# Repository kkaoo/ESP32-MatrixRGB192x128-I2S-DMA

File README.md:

# RGBMatrixPanel library for the ESP32, utilising I2S DMA

得到[mrfaptastic](https://github.com/mrfaptastic/ESP32-RGB64x32MatrixPanel-I2S-DMA)启发, fork并扩展了功能：

* 修改了IO映射，留出SPI接口可以扩展连接树莓派
* 关掉了双buffer功能，留存更多的RAM来扩展更大的显示屏：192x128
* 受SPI接口速度限制，外部SPI显示传输刷新率只有20HZ
* RAM限制和DMA输出频率限制，RGB Panel刷新率只有70HZ，会有一点闪烁感
* can theoretically provide 5 bit colour: RGB555

## Usage

* 如果不需要那么高的亮度，可以将亮度调低减小电流:
`matrix.setPanelBrightness(8);`
* 注意有的面板LED接口顺序是RGB，有的则是BGR，还有RBG，有时需要调整IO，可以在直接matrix.begin()函数重新分配IO
`matrix.begin(R1,G1,B1,R2,G2,B2.....)`
* 暂时没测试FM612X系列驱动IC的面板，这类IC比较特殊，需要定义锁存脉冲个数
* 开发环境PlatformIO
* 如果连接6个面板，我是这样排列的

* 测试64x64的效果[examples/test_64x64/test_64x64.cpp]

`#define mw 64`

`#define mh 64`

* 测试192x128的效果[examples/test_192x128/test_192x128.cpp]

`#define mw 192`

`#define mh 128`

## Circuit & PCB

By default the pin mapping is as follows (defaults defined in ESP32-RGBMatrixPanel-I2S-DMA.h).

请注意线路是按单个面板画的（64x64），如果拼接多个面板，电源需要加强加强再加强。即单独外加5V/3A以上电源。

## 连接树莓派或其它

通过SPI接口连接到树莓派，RGBMatrixPanel模拟成一块SPI TFT显示屏。

......待续

## Credits

* ['ESP32-RGB64x32MatrixPanel-I2S-DMA' library](https://github.com/mrfaptastic/ESP32-RGB64x32MatrixPanel-I2S-DMA)
* ['SmartMatrix' project code](https://github.com/pixelmatix/SmartMatrix/tree/teensylc)
* [Sprite_TM's demo implementation here](https://www.esp32.com/viewtopic.php?f=17&t=3188)

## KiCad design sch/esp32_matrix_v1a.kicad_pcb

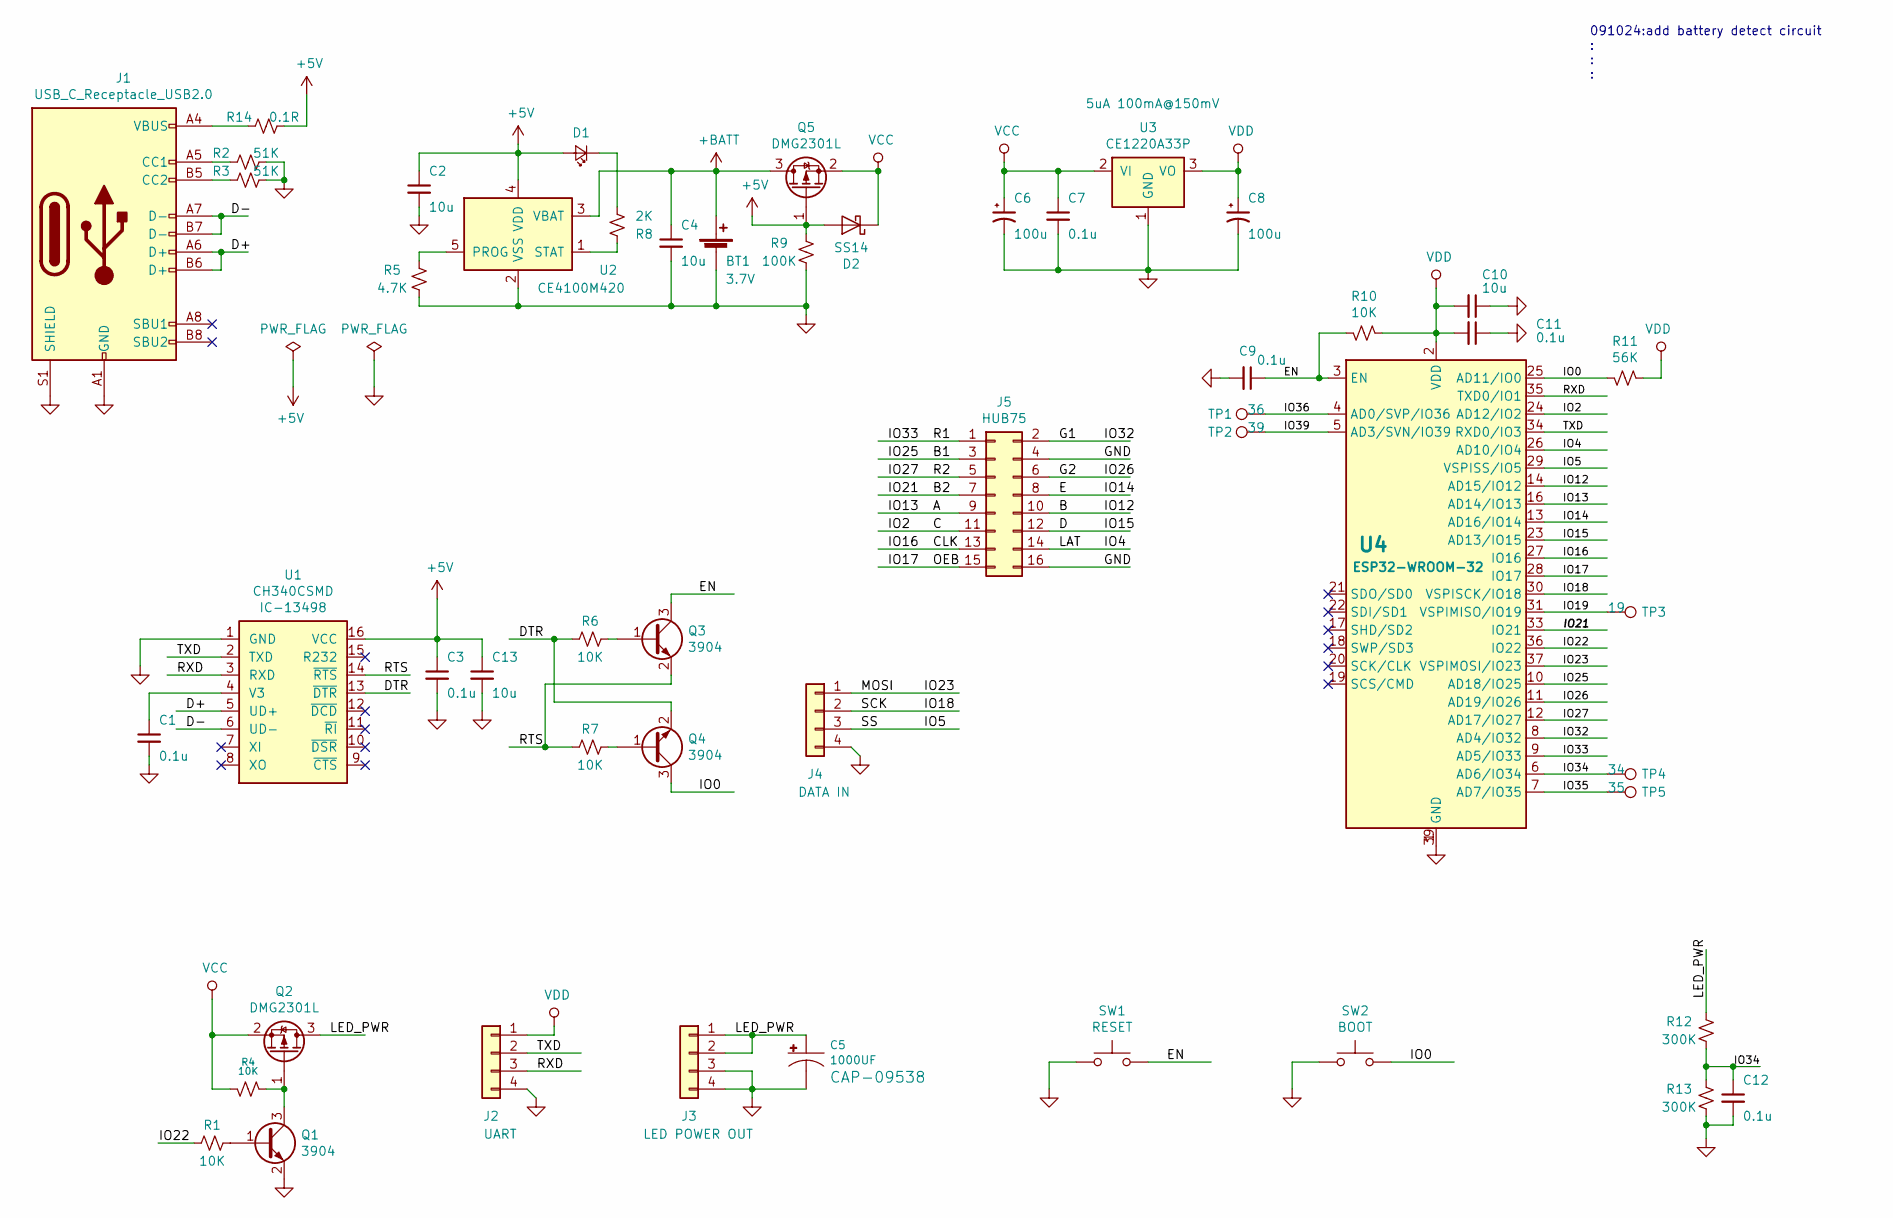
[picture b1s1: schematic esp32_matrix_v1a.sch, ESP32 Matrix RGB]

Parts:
BT1: 3.7V; JST_PH_B2B-PH-K_1x02_P2.00mm_Vertical
C1, C3, C7, C9, C11, C12: 0.1u; 0603_C
C2, C4, C10, C13: 10u; 0805_C
C5: 1000UF; CPOL-RADIAL-5MM-10MM
C6, C8: 100u; CP_EIA-3528-15_AVX-H
D1: LED_Small; LED_0805_2012Metric
D2: SS14; D_SMA
J1: USB_C_Receptacle_USB2.0; USB_C_Receptacle_Palconn_UTC16-G
J2: UART; 1X04_NO_SILK
J3: LED POWER OUT; 1X04_NO_SILK
J4: DATA IN; 1X04_NO_SILK
J5: HUB75; PinSocket_2x08_P2.54mm_Vertical
Q1, Q3, Q4: 3904; SOT-23
Q2, Q5: DMG2301L; SOT-23
R1, R4, R6, R7, R10: 10K; 0603_R
R2, R3: 51K; 0603_R
R5: 4.7K; 0603_R
R8: 2K; 0603_R
R9: 100K; 0603_R
R11: 56K; 0603_R
R12, R13: 300K; 0603_R
R14: 0.1R; 0603_R
SW1: RESET; SW_Push_1P1T_NO_CK_KSC6xxJ
SW2: BOOT; SW_Push_1P1T_NO_CK_KSC6xxJ
TP1: 36; TestPoint_Pad_D1.0mm
TP2: 39; TestPoint_Pad_D1.0mm
TP3: 19; TestPoint_Pad_D1.0mm
TP4: 34; TestPoint_Pad_D1.0mm
TP5: 35; TestPoint_Pad_D1.0mm
U1: CH340CSMD; SO16
U2: CE4100M420; SOT-23-5
U3: CE1220A33P; SOT-89-3
U4: ESP32-WROOM-32

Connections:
+BATT: BT1.1 (+), C4.1, Q5.3 (D), U2.3 (VBAT)
/A: J5.9, U4.16 (AD14/IO13)
/B: J5.10, U4.14 (AD15/IO12)
/BD1: J5.3, U4.10 (AD18/IO25)
/BD2: J5.7, U4.33 (IO21)
/C: J5.11, U4.24 (AD12/IO2)
/CLK: J5.13, U4.27 (IO16)
/D: J5.12, U4.23 (AD13/IO15)
/D+: J1.A6 (D+), J1.B6 (D+), U1.5 (UD+)
/D-: J1.A7 (D-), J1.B7 (D-), U1.6 (UD-)
/DTR: Q4.2 (E), R6.2, U1.13 (~DTR)
/E: J5.8, U4.13 (AD16/IO14)
/EN: C9.1, Q3.3 (C), R10.1, SW1.2, U4.3 (EN)
/GD1: J5.2, U4.8 (AD4/IO32)
/GD2: J5.6, U4.11 (AD19/IO26)
/IO0: Q4.3 (C), R11.1, SW2.2, U4.25 (AD11/IO0)
/IO4: J5.14, U4.26 (AD10/IO4)
/IO5: J4.3, U4.29 (VSPISS/IO5)
/IO17: J5.15, U4.28 (IO17)
/IO18: J4.2, U4.30 (VSPISCK/IO18)
/IO19: TP3.1, U4.31 (VSPIMISO/IO19)
/IO22: R1.2, U4.36 (IO22)
/IO23: J4.1, U4.37 (VSPIMOSI/IO23)
/IO27: J5.5, U4.12 (AD17/IO27)
/IO33: J5.1, U4.9 (AD5/IO33)
/IO34: C12.1, R12.1, R13.2, TP4.1, U4.6 (AD6/IO34)
/IO35: TP5.1, U4.7 (AD7/IO35)
/IO36: TP1.1, U4.4 (AD0/SVP/IO36)
/IO39: TP2.1, U4.5 (AD3/SVN/IO39)
/LED_PWR: C5.+, J3.1, J3.2, Q2.3 (D), R12.2
/RTS: Q3.2 (E), R7.2, U1.14 (~RTS)
/RXD: J2.3, U1.3 (RXD), U4.35 (TXD0/IO1)
/TXD: J2.2, U1.2 (TXD), U4.34 (RXD0/IO3)
GND: BT1.2 (-), C1.2, C2.2, C3.2, C4.2, C5.-, C6.2, C7.2, C8.2, C9.2, C10.1, C11.1, C12.2, C13.2, J1.A1 (GND), J1.A12 (GND), J1.B1 (GND), J1.B12 (GND), J1.S1 (SHIELD), J2.4, J3.3, J3.4, J4.4, J5.4, J5.16, Q1.2 (E), R2.1, R3.1, R5.1, R9.1, R13.1, SW1.1, SW2.1, U1.1 (GND), U2.2 (VSS), U3.1 (GND), U4.1 (GND), U4.15 (GND), U4.38 (GND), U4.39 (GND)
unnamed: C1.1, U1.4 (V3)
unnamed: D1.1 (K), R8.1
unnamed: J1.A5 (CC1), R2.2
unnamed: J1.B5 (CC2), R3.2
unnamed: Q1.1 (B), R1.1
unnamed: Q1.3 (C), Q2.1 (G), R4.2
unnamed: Q3.1 (B), R6.1
unnamed: Q4.1 (B), R7.1
unnamed: R5.2, U2.5 (PROG)
unnamed: R8.2, U2.1 (STAT)
VCC: C6.1, C7.1, D2.1 (K), Q2.2 (S), Q5.2 (S), R4.1, U3.2 (VI)
VDD: C8.1, C10.2, C11.2, J2.1, R10.2, R11.2, U3.3 (VO), U4.2 (VDD)

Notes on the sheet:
091024:add battery detect circuit : : :

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
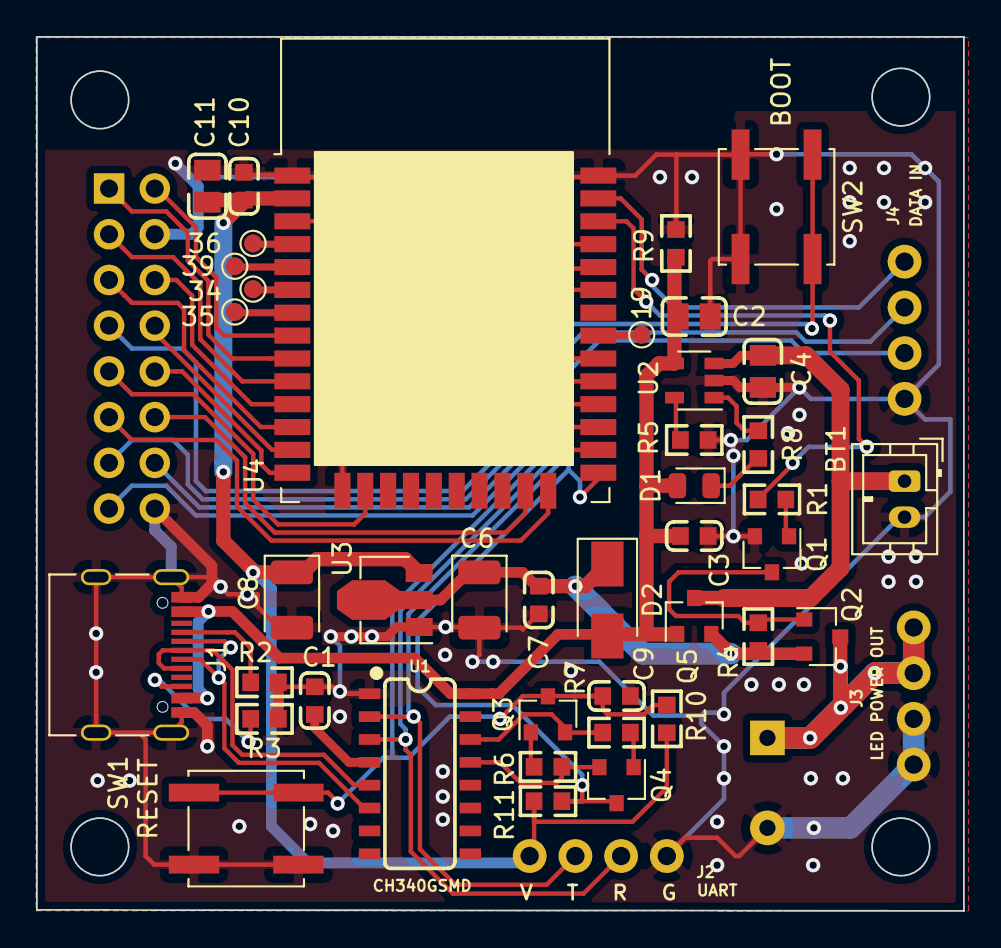
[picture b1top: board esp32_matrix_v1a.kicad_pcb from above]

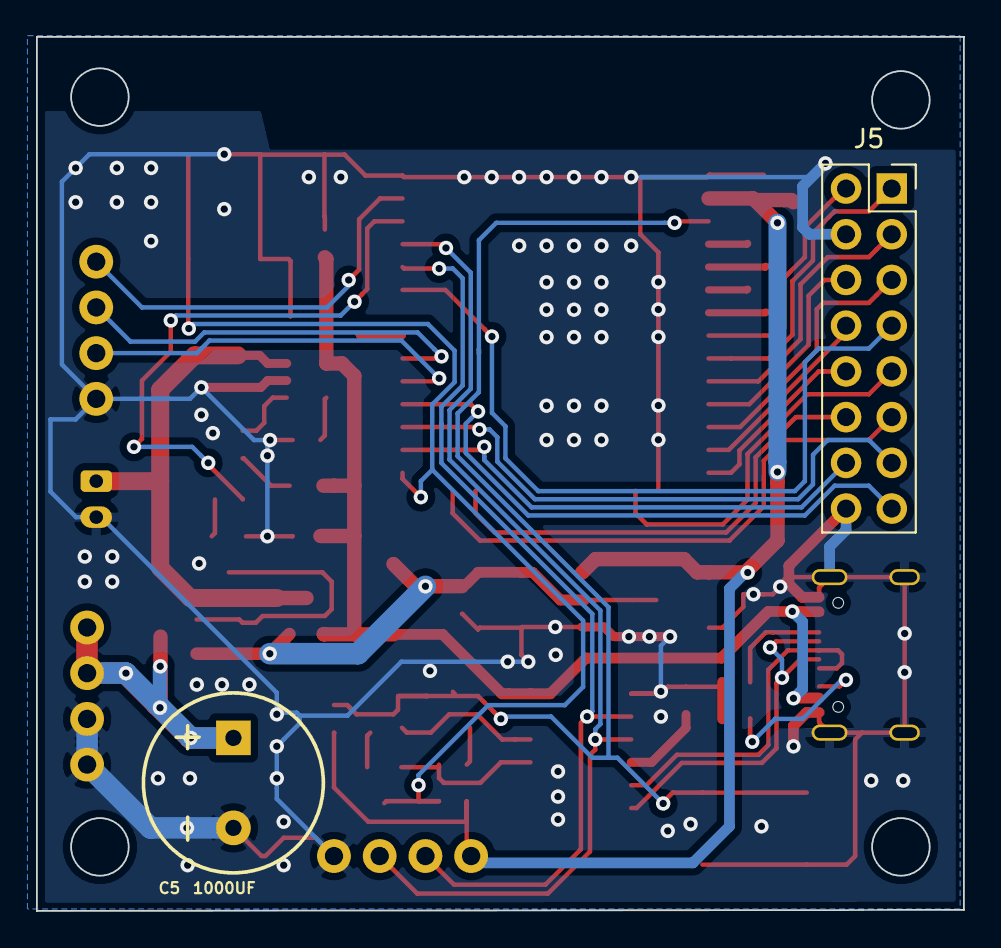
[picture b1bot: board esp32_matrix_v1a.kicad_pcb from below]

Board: 2 copper layers, 51.5 x 48.6 mm, 46 parts (2 on the bottom side), 47 nets.

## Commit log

2019-10-30 First version : gooood
2019-10-30 /\ 192x128 : First Version /\
2019-11-04 Optimize the library and add examples
